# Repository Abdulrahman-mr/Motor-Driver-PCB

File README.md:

## Motor-Driver-PCB

This project contains the PCB design files (schematic and board layout) for the L298N motor driver circuit board I've created using Autodesk Eagle. The fabrication method uses UV exposure ([https://en.wikipedia.org/wiki/UV_curing](https://en.wikipedia.org/wiki/UV_curing)) with a laminator, UV oven, sodium hydroxide (etchant), and baking soda for neutralization. The final fabricated PCB is also provided.

### Files/Folders Description

* **Illustrations and Output folder:** Contains images capturing the development stages of the project.
* **Design Folder:** Contains the Motor Driver board layout file and the schematic diagram.
* **BOM:** Bill of Materials listing the components used in this board.
* **CircuitDiagram:** The circuit diagram of the project.
* **Pads Drill size guide Diagram:** The drill guide (printable) for the PCB.

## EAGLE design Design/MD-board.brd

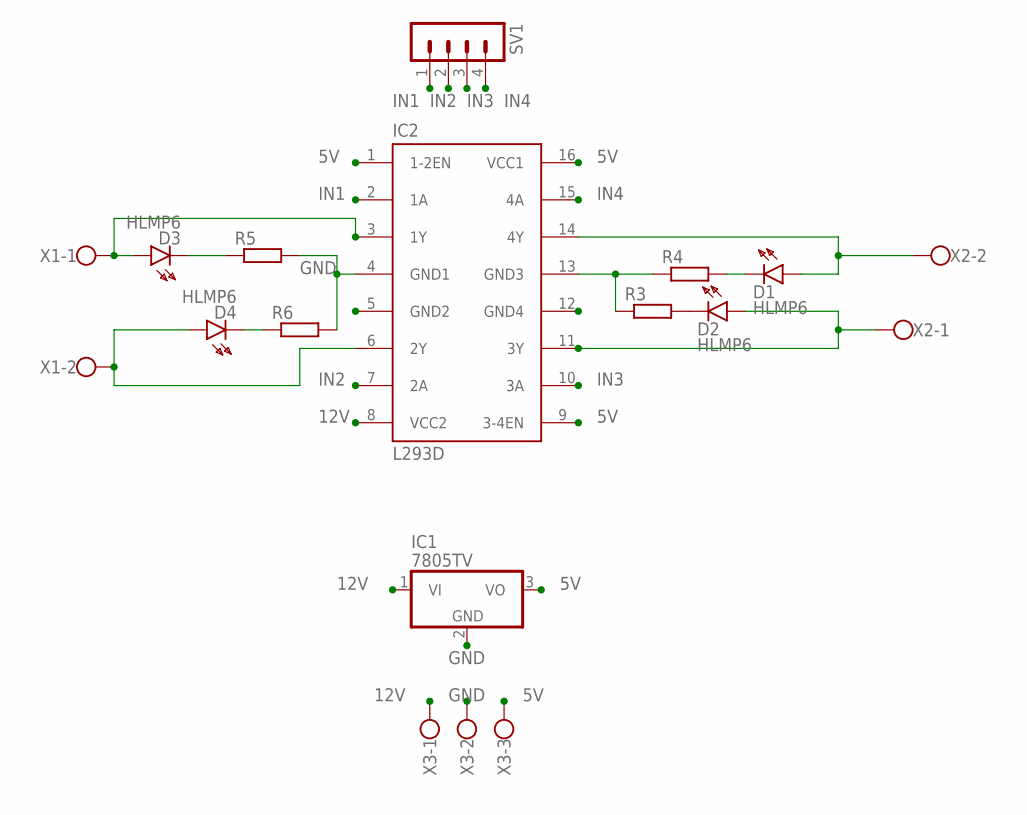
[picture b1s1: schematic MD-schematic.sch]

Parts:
D1, D2, D3, D4: HLMP6
IC1: 7805TV; TO220V
IC2: L293D; DIL16
R3, R4, R5, R6: R-EU_0204/5; 0204/5
SV1: MA04-1
X1, X2: W237-102
X3: W237-103

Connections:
5V: IC1.3 (VO), IC2.1 (1-2EN), IC2.9 (3-4EN), IC2.16 (VCC1), X3.3
12V: IC1.1 (VI), IC2.8 (VCC2), X3.1
GND: IC1.2 (GND), IC2.4 (GND1), R5.2, R6.2, X3.2
IN1: IC2.2 (1A), SV1.1
IN2: IC2.7 (2A), SV1.2
IN3: IC2.10 (3A), SV1.3
IN4: IC2.15 (4A), SV1.4
unnamed: D1.K, R4.2
unnamed: D1.A, IC2.14 (4Y), X2.2
unnamed: IC2.13 (GND3), R3.1, R4.1
unnamed: D2.K, R3.2
unnamed: D3.K, R5.1
unnamed: D4.A, IC2.6 (2Y), X1.2
unnamed: D4.K, R6.1
OUT1: D3.A, IC2.3 (1Y), X1.1
OUT4: D2.A, IC2.11 (3Y), X2.1

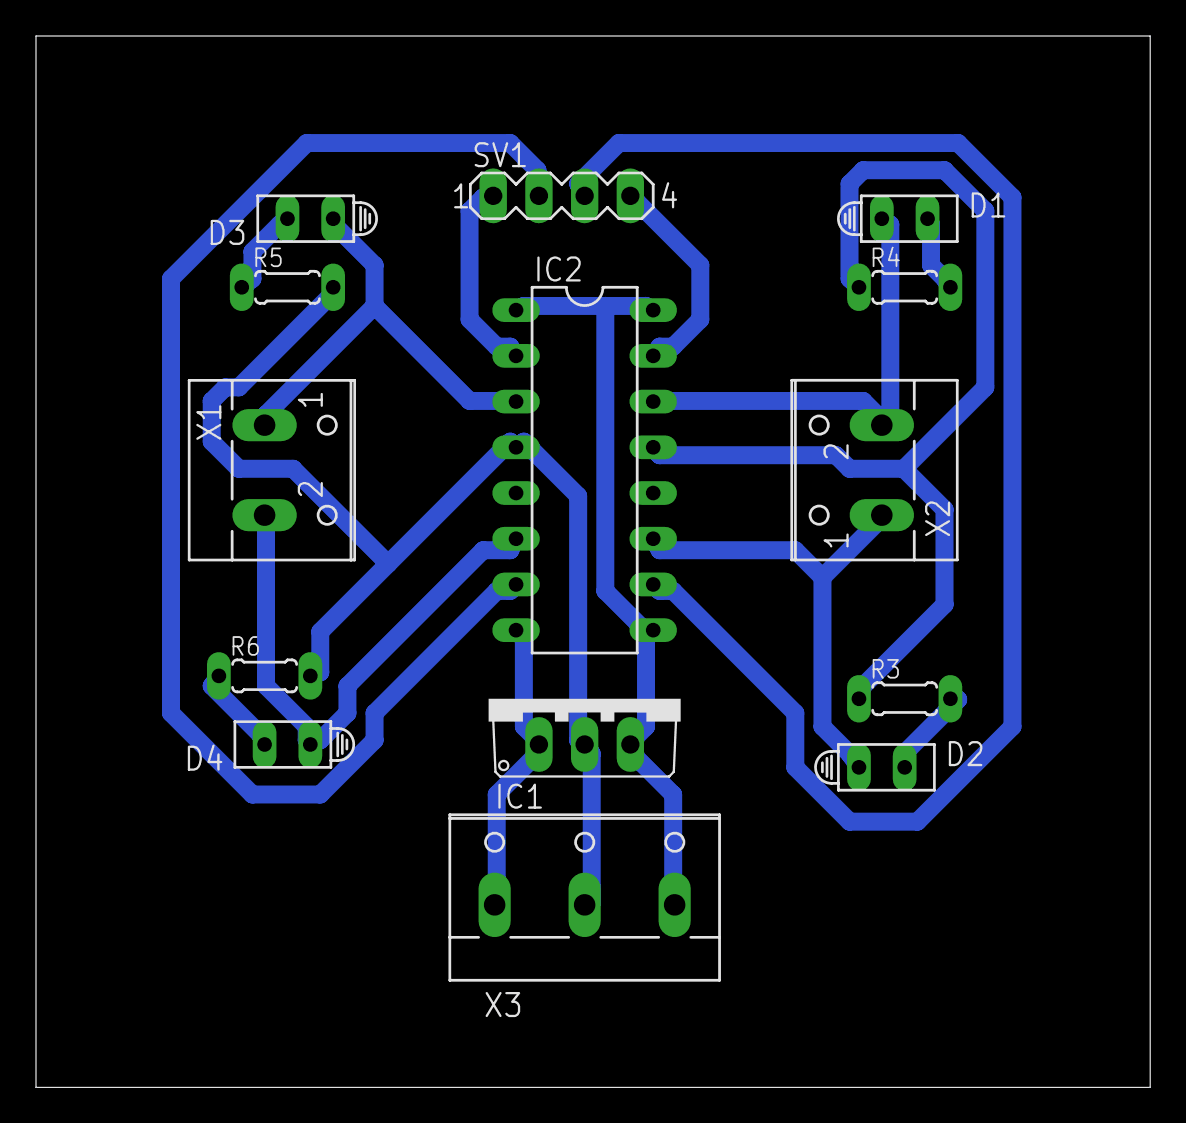
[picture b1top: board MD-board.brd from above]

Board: 2 copper layers, 61.9 x 58.4 mm, 14 parts (0 on the bottom side), 16 nets.

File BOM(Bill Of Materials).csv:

"Qty";"Value";"Device";"Package";"Parts";"Description";"MF";"MPN";"OC_FARNELL";"OC_NEWARK";"POPULARITY";"SPICEPREFIX";
"1";"";"MA04-1";"MA04-1";"SV1";"PIN HEADER";"";"";"unknown";"unknown";"41";"";
"4";"";"R-EU_0204/5";"0204/5";"R3, R4, R5, R6";"RESISTOR, European symbol";"";"";"";"";"35";"R";
"2";"";"W237-102";"W237-102";"X1, X2";"WAGO SCREW CLAMP";"";"237-102";"unknown";"70K9898";"32";"";
"1";"";"W237-103";"W237-103";"X3";"WAGO SCREW CLAMP";"";"237-103";"unknown";"18M7116";"5";"";
"1";"7805TV";"7805TV";"TO220V";"IC1";"Positive VOLTAGE REGULATOR";"";"";"";"";"57";"";
"4";"HLMP6";"HLMP6";"HLMP6";"D1, D2, D3, D4";"LED";"AGILENT TECHNOLOGIES";"HLMP-6500";"1652490";"40K0088";"6";"";
"1";"L293D";"L293D";"DIL16";"IC2";"PUSH-PULL 4 CHANNEL DRIVER";"";"L293D";"9589619";"56P8249";"16";"";

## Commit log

2024-04-29 Create dd
